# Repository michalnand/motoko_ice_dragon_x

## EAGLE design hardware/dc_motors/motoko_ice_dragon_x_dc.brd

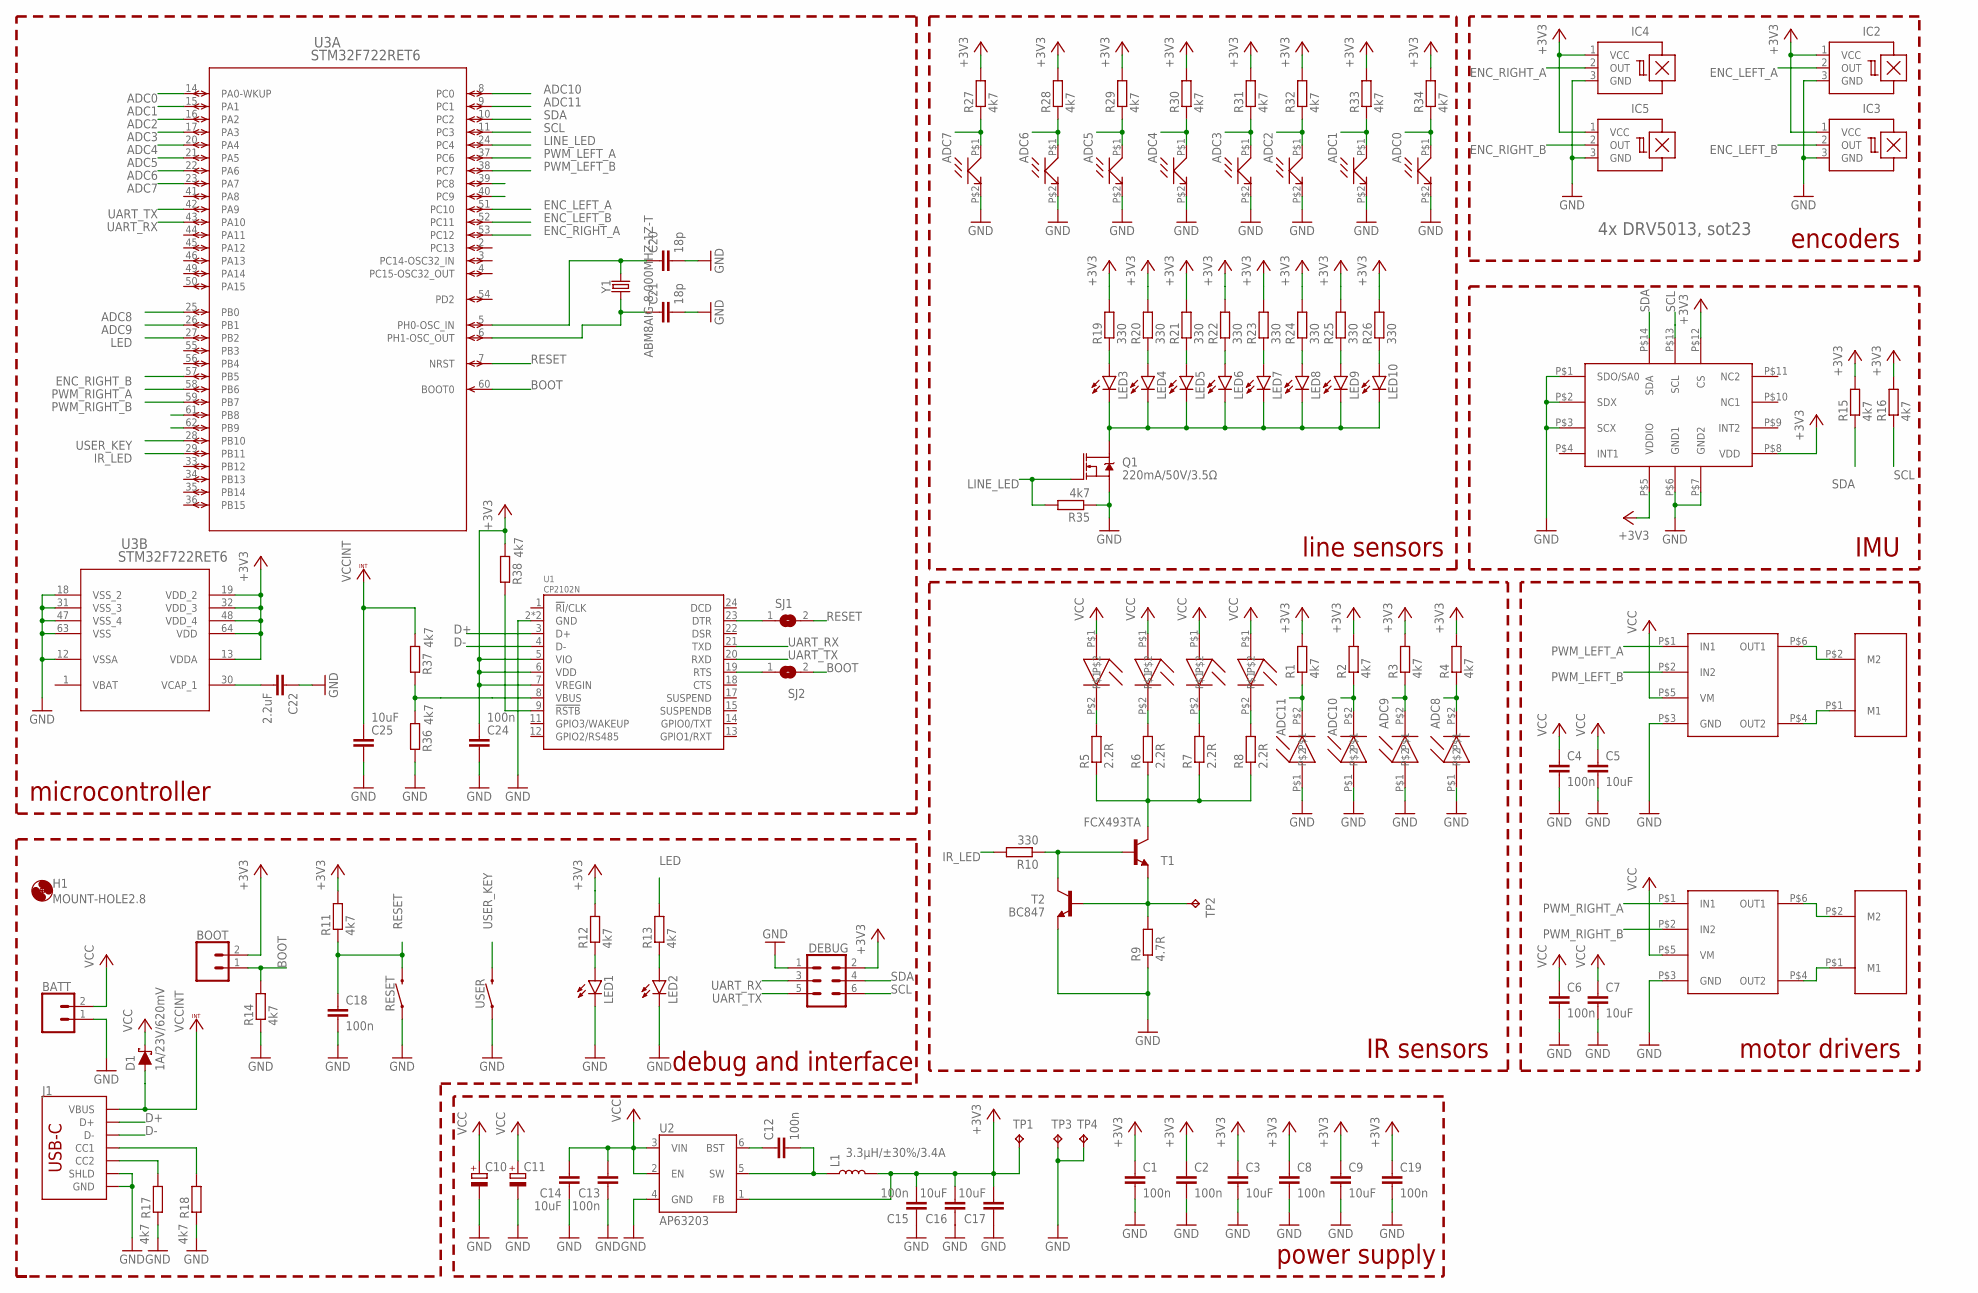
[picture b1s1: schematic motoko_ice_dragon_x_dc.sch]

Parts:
BATT: CONN_02LOCK_LONGPADS; 1X02_LOCK_LONGPADS
BOOT: CONN_02LOCK_LONGPADS; 1X02_LOCK_LONGPADS
C1, C2, C4, C6, C8, C12, C13, C15, C18, C19, C24: 100n; C0805
C3, C5, C7, C9, C14, C16, C17, C25: 10uF; C0805
C10, C11: CPOL-EU140CLH-0810; 140CLH-0810
C20, C21: 18p; C0805
C22: 2.2uF; C0805
D1: 1A/23V/620mV; SOD-323
DEBUG: FEMALE 2x3; 2X3
H1: MOUNT-HOLE2.8; 2,8
IC2, IC3, IC4, IC5: A1202LH; SOT23-W
J1: 640-USB4105-GF-A-120, man. GCT; USB-C-16P-2LAYER-PADS
L1: 3.3µH/±30%/3.4A; CR54
LED1, LED2, LED3, LED4, LED5, LED6, LED7, LED8, LED9, LED10: LEDCHIPLED_1206; CHIPLED_1206
Q1: 220mA/50V/3.5Ω; SOT23-3
R1, R2, R3, R4, R11, R12, R13, R14, R15, R16, R17, R18, R27, R28, R29, R30, R31, R32, R33, R34, R35, R36, R37, R38: 4k7; M0805
R5, R6, R7, R8: 2.2R; M0805
R9: 4.7R; M0805
R10, R19, R20, R21, R22, R23, R24, R25, R26: 330; M0805
RESET: MOMENTARY-SWITCH-SPST-SMD-6.2MM-TALL; TACTILE_SWITCH_SMD_6.2MM_TALL
SJ1, SJ2: SJ
T1: FCX493TA; SOT89-BCE
T2: BC847; SOT23
TP1, TP2, TP3, TP4: TPB1,27; B1,27
U1: CP2102N; QFN24
U2: AP63203; SOT23-6
U3: STM32F722RET6; LQFP64-10X10MM
U$1, U$3: DRV8212; SOT_0.6MM
U$2, U$15, U$16, U$17, U$18, U$19, U$20, U$21: SFH3710; SFH710
U$4, U$5: POLOLU_MICRO_METAL_GEAR_MOTOR
U$6: LSM6DSM; LGA14L
U$7, U$8, U$9, U$10, U$11, U$12, U$13, U$14: LED_5MM_AXIAL
USER: MOMENTARY-SWITCH-SPST-SMD-6.2MM-TALL; TACTILE_SWITCH_SMD_6.2MM_TALL
Y1: ABM8AIG-8.000MHZ-1Z-T; CRYSTAL-SMD-3.2X2.5MM

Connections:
+3V3: BOOT.2, C1.1, C2.1, C3.1, C8.1, C9.1, C15.2, C16.2, C17.2, C19.1, C24.1, DEBUG.2, IC2.1 (VCC), IC3.1 (VCC), IC4.1 (VCC), IC5.1 (VCC), L1.P$2 (2), R1.2, R2.2, R3.2, R4.2, R11.2, R12.2, R15.2, R16.2, R19.2, R20.2, R21.2, R22.2, R23.2, R24.2, R25.2, R26.2, R27.2, R28.2, R29.2, R30.2, R31.2, R32.2, R33.2, R34.2, R38.1, TP1.TP, U1.5 (VIO), U1.6 (VDD), U1.7 (VREGIN), U2.1 (FB), U3.13 (VDDA), U3.19 (VDD_2), U3.32 (VDD_3), U3.48 (VDD_4), U3.64 (VDD), U$6.P$5 (VDDIO), U$6.P$8 (VDD), U$6.P$12 (CS)
ADC0: R34.1, U3.14 (PA0-WKUP), U$21.P$1 (C)
ADC1: R33.1, U3.15 (PA1), U$20.P$1 (C)
ADC2: R32.1, U3.16 (PA2), U$19.P$1 (C)
ADC3: R31.1, U3.17 (PA3), U$18.P$1 (C)
ADC4: R30.1, U3.20 (PA4), U$17.P$1 (C)
ADC5: R29.1, U3.21 (PA5), U$16.P$1 (C)
ADC6: R28.1, U3.22 (PA6), U$15.P$1 (C)
ADC7: R27.1, U3.23 (PA7), U$2.P$1 (C)
ADC8: R4.1, U3.25 (PB0), U$7.P$2
ADC9: R3.1, U3.26 (PB1), U$11.P$2
ADC10: R2.1, U3.8 (PC0), U$14.P$2
ADC11: R1.1, U3.9 (PC1), U$9.P$2
BOOT: BOOT.1, R14.2, SJ2.2, U3.60 (BOOT0)
D+: J1.A6 (D+), J1.B6 (D+), U1.3 (D+)
D-: J1.A7 (D-), J1.B7 (D-), U1.4 (D-)
ENC_LEFT_A: IC2.2 (OUT), U3.51 (PC10)
ENC_LEFT_B: IC3.2 (OUT), U3.52 (PC11)
ENC_RIGHT_A: IC4.2 (OUT), U3.53 (PC12)
ENC_RIGHT_B: IC5.2 (OUT), U3.57 (PB5)
GND: BATT.1, C1.2, C2.2, C3.2, C4.2, C5.2, C6.2, C7.2, C8.2, C9.2, C10.-, C11.-, C13.1, C14.1, C15.1, C16.1, C17.1, C18.2, C19.2, C20.2, C21.2, C22.1, C24.2, C25.2, DEBUG.1, IC2.3 (GND), IC3.3 (GND), IC4.3 (GND), IC5.3 (GND), J1.GND, J1.GND2 (GND), J1.SHLD1 (SHLD), J1.SHLD2 (SHLD), J1.SHLD3 (SHLD), J1.SHLD4 (SHLD), LED1.C, LED2.C, Q1.2 (S), R9.1, R14.1, R17.1, R18.1, R35.1, R36.2, RESET.A2 (1), T2.2 (E), TP3.TP, TP4.TP, U1.2 (GND), U1.PAD (GND), U2.4 (GND), U3.12 (VSSA), U3.18 (VSS_2), U3.31 (VSS_3), U3.47 (VSS_4), U3.63 (VSS), U$1.P$3 (GND), U$2.P$2 (E), U$3.P$3 (GND), U$6.P$1 (SDO/SA0), U$6.P$2 (SDX), U$6.P$3 (SCX), U$6.P$6 (GND1), U$6.P$7 (GND2), U$7.P$1, U$9.P$1, U$11.P$1, U$14.P$1, U$15.P$2 (E), U$16.P$2 (E), U$17.P$2 (E), U$18.P$2 (E), U$19.P$2 (E), U$20.P$2 (E), U$21.P$2 (E), USER.A2 (1)
IR_LED: R10.2, U3.29 (PB11)
LED: R13.2, U3.27 (PB2)
LINE_LED: Q1.1 (G), R35.2, U3.24 (PC4)
unnamed: U$1.P$6 (OUT1), U$4.P$2 (M2)
unnamed: U$1.P$4 (OUT2), U$4.P$1 (M1)
unnamed: U$3.P$6 (OUT1), U$5.P$2 (M2)
unnamed: U$3.P$4 (OUT2), U$5.P$1 (M1)
unnamed: R5.2, U$10.P$2
unnamed: R6.2, U$13.P$2
unnamed: R7.2, U$12.P$2
unnamed: R8.2, U$8.P$2
unnamed: SJ2.1, U1.19 (RTS)
unnamed: R9.2, T1.E, T2.1 (B), TP2.TP
unnamed: J1.B5 (CC2), R17.2
unnamed: C12.1, U2.6 (BST)
unnamed: C12.2, L1.P$1 (1), U2.5 (SW)
unnamed: R10.1, T1.B, T2.3 (C)
unnamed: R5.1, R6.1, R7.1, R8.1, T1.C
unnamed: LED1.A, R12.1
unnamed: LED2.A, R13.1
unnamed: J1.A5 (CC1), R18.2
unnamed: C20.1, U3.5 (PH0-OSC_IN), Y1.3 (2)
unnamed: C21.1, U3.6 (PH1-OSC_OUT), Y1.1
unnamed: LED3.A, R19.1
unnamed: LED4.A, R20.1
unnamed: C22.2, U3.30 (VCAP_1)
unnamed: LED5.A, R21.1
unnamed: LED6.A, R22.1
unnamed: LED7.A, R23.1
unnamed: LED8.A, R24.1
unnamed: LED9.A, R25.1
unnamed: LED10.A, R26.1
unnamed: LED3.C, LED4.C, LED5.C, LED6.C, LED7.C, LED8.C, LED9.C, LED10.C, Q1.3 (D)
unnamed: SJ1.1, U1.23 (DTR)
unnamed: R38.2, U1.9 (!RSTB)
unnamed: R36.1, R37.2, U1.8 (VBUS)
PWM_LEFT_A: U3.37 (PC6), U$1.P$1 (IN1)
PWM_LEFT_B: U3.38 (PC7), U$1.P$2 (IN2)
PWM_RIGHT_A: U3.58 (PB6), U$3.P$1 (IN1)
PWM_RIGHT_B: U3.59 (PB7), U$3.P$2 (IN2)
RESET: C18.1, R11.1, RESET.B2 (2), SJ1.2, U3.7 (NRST)
SCL: DEBUG.6, R16.1, U3.11 (PC3), U$6.P$13 (SCL)
SDA: DEBUG.4, R15.1, U3.10 (PC2), U$6.P$14 (SDA)
UART_RX: DEBUG.3, U1.21 (TXD), U3.43 (PA10)
UART_TX: DEBUG.5, U1.20 (RXD), U3.42 (PA9)
USER_KEY: U3.28 (PB10), USER.B2 (2)
VBAT: U3.1 (VBAT)
VCC: BATT.2, C4.1, C5.1, C6.1, C7.1, C10.+, C11.+, C13.2, C14.2, D1.C, U2.2 (EN), U2.3 (VIN), U$1.P$5 (VM), U$3.P$5 (VM), U$8.P$1, U$10.P$1, U$12.P$1, U$13.P$1
VCCINT: C25.1, D1.A, J1.VBUS1 (VBUS), J1.VBUS2 (VBUS), R37.1

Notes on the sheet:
4x DRV5013, sot23
line sensors
encoders
IMU
motor drivers
IR sensors
power supply
debug and interface
microcontroller

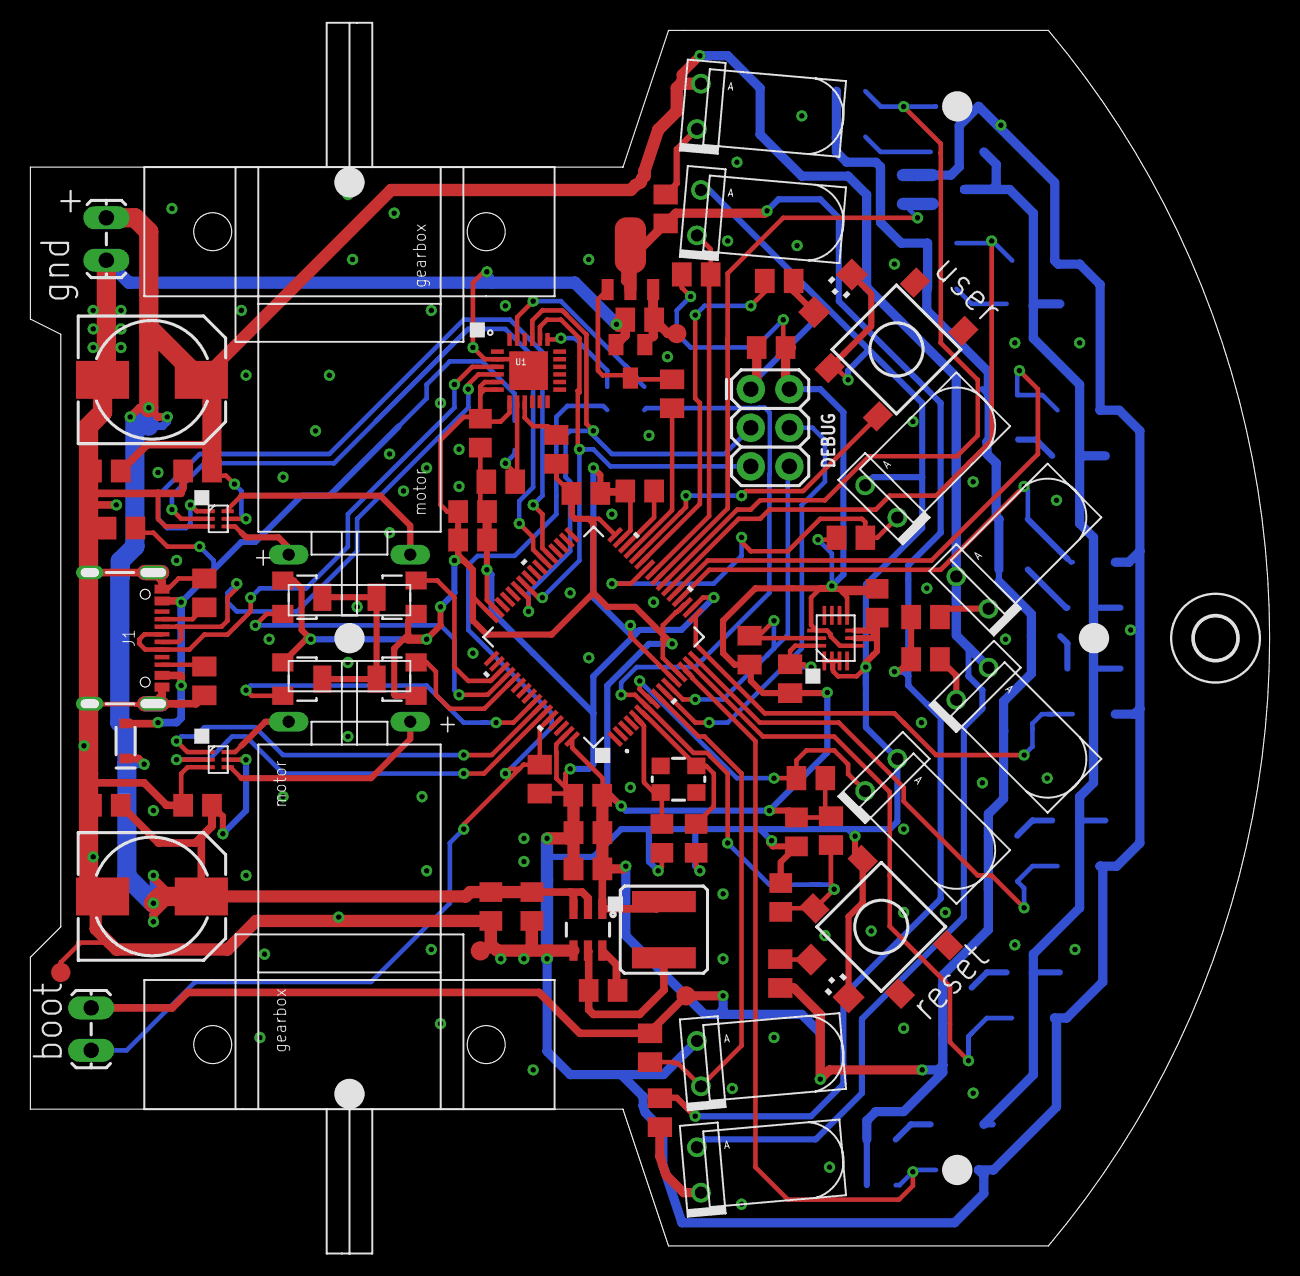
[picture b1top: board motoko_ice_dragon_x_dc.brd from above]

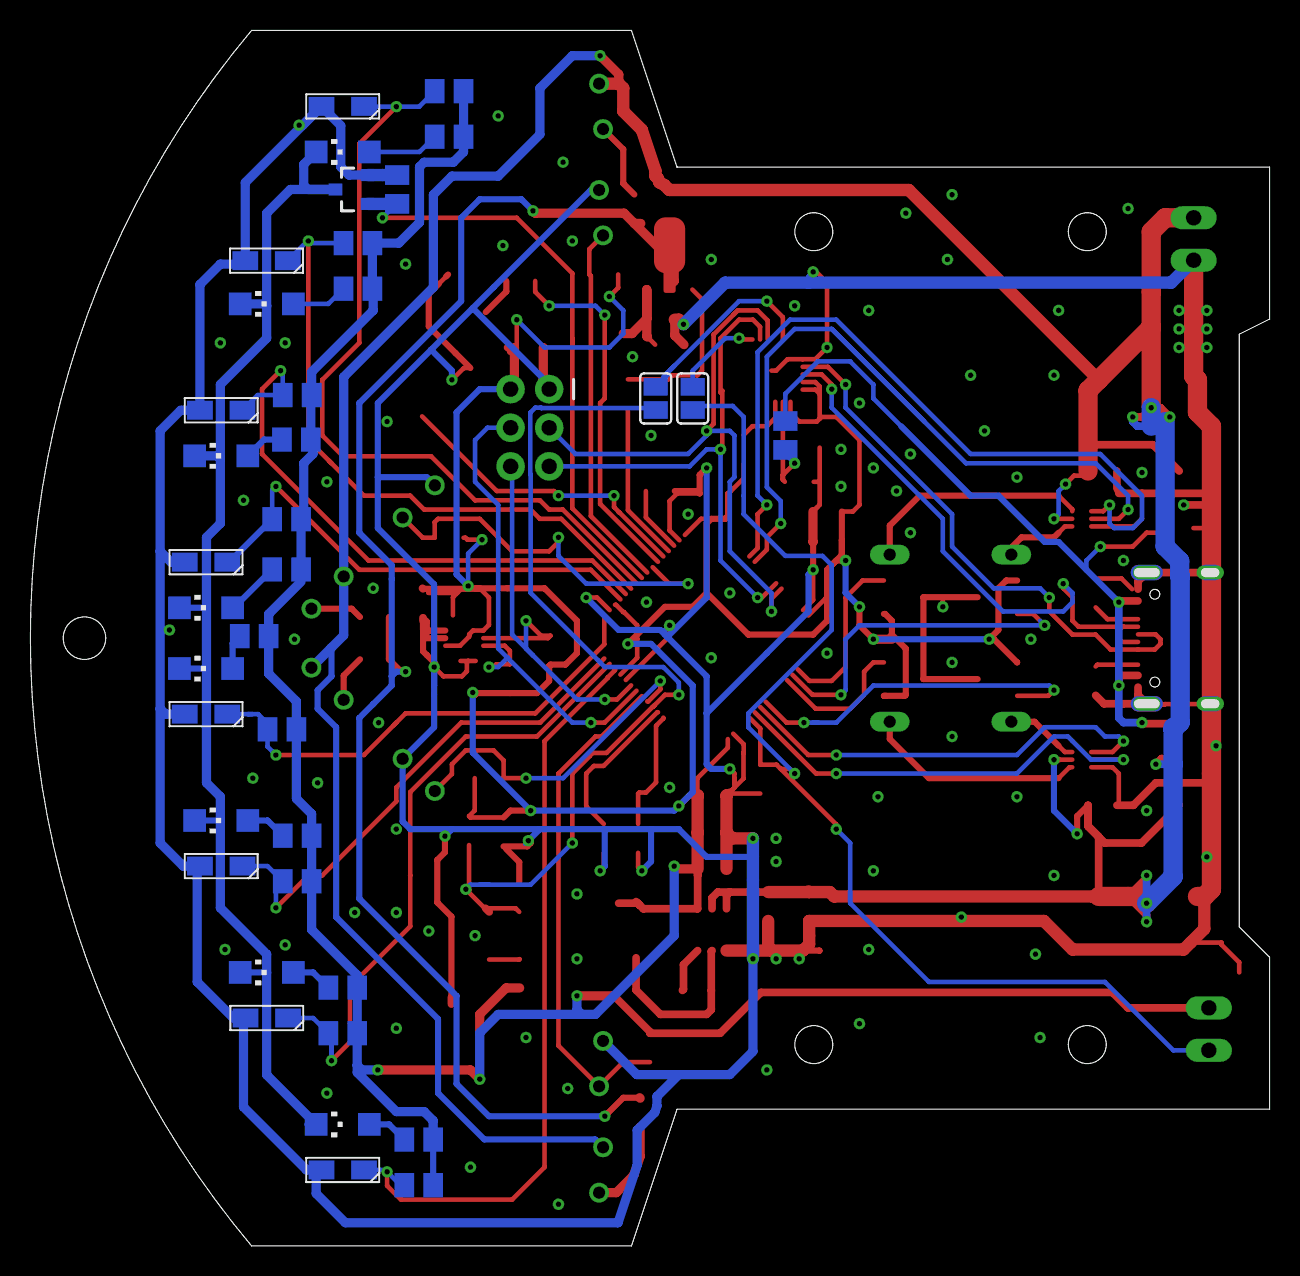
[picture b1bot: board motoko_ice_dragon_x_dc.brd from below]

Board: 2 copper layers, 81.0 x 79.4 mm, 119 parts (37 on the bottom side), 69 nets.

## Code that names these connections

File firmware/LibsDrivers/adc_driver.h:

#ifndef _ADC_DRIVER_H_
#define _ADC_DRIVER_H_ 

#define ADC_CHANNELS_COUNT      ((uint32_t)(8 + 4))

#define LINE_SENSOR_OFFSET      ((uint32_t)(0))
#define IR_SENSOR_OFFSET        ((uint32_t)(8))


//line sensors physical channels
#define ADC_LINE_0                 (LL_ADC_CHANNEL_0)    //PA0   - right sensor
#define ADC_LINE_1                 (LL_ADC_CHANNEL_1)    //PA1
#define ADC_LINE_2                 (LL_ADC_CHANNEL_2)    //PA2
#define ADC_LINE_3                 (LL_ADC_CHANNEL_3)    //PA3
#define ADC_LINE_4                 (LL_ADC_CHANNEL_4)    //PA4
#define ADC_LINE_5                 (LL_ADC_CHANNEL_5)    //PA5
#define ADC_LINE_6                 (LL_ADC_CHANNEL_6)    //PA6
#define ADC_LINE_7                 (LL_ADC_CHANNEL_7)    //PA7   - left sensor

//IR sensors physical channels
#define ADC_IR_FRONT_LEFT           (LL_ADC_CHANNEL_8)    //PB0
#define ADC_IR_LEFT                 (LL_ADC_CHANNEL_9)    //PB1
#define ADC_IR_RIGHT                (LL_ADC_CHANNEL_10)   //PC0
#define ADC_IR_FRONT_RIGHT          (LL_ADC_CHANNEL_11)   //PC1

  
class ADC_driver
{
    public:
        ADC_driver();

        void init();
        uint16_t* get();

        void callback();

    public:    
        uint32_t adc_current_idx;
        uint32_t adc_channels[ADC_CHANNELS_COUNT];
        uint16_t adc_result[ADC_CHANNELS_COUNT];

        uint32_t measurement_id;
};

#endif

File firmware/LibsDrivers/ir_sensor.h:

#ifndef _IR_SENSOR_H_
#define _IR_SENSOR_H_

#include <drivers.h>
#include <stdint.h>
#include <array.h>


#define IR_SENSORS_COUNT        ((unsigned int)4)


/*
    IR left         :   PB1     ADC1, ADC2, IN9
    IR front left   :   PC5     ADC1, ADC2, IN15
    IR front right  :   PC4     ADC1, ADC2, IN14
    IR right        :   PB0     ADC1, ADC2, IN8
*/

class IRSensor
{
    public:
        void init();

        void callback();

        float obstacle_distance();
        int obstacle_detected();
            
    private:
        float calibration(float *callibration, float x);

    public:
        uint32_t measurement_id;

    private: 
        uint32_t state;
        Gpio<'B', 11, GPIO_MODE_OUT> ir_led; 

        Array<int, IR_SENSORS_COUNT> ir_off;
        Array<int, IR_SENSORS_COUNT> ir_on;

        float filter_coeff;
            
    public:
        Array<float, IR_SENSORS_COUNT> distance;

};

#endif

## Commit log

2024-06-15 initial + hw
2024-06-15 documentation
2024-06-16 firmware
2024-06-16 bldc version
2024-06-19 firmware tests
2024-06-19 tests
2024-06-20 tests + images
2024-06-21 ir sensors
2024-06-23 encoder fix
2024-07-18 simulation
2024-07-30 demos + tests
2024-08-07 motor control, motor identification
2024-08-08 identification demo
2024-08-15 better encoder
2024-09-15 pid example
2024-10-28 kalman filter for encoder
2024-10-29 motor test
2024-11-22 bldc test
2024-11-26 mpc simulation
2025-03-02 position control
2025-03-10 position controller, model identifiction
2025-03-13 new motor control
2025-03-14 path planner
2025-03-15 acc control
2025-03-18 line following
2025-03-23 mpc line following
2025-03-27 fast line following
2025-03-30 line following + broken line
2025-04-01 brick avoid
2025-04-04 line follower
2025-04-21 working code
2025-04-26 istrobot 2025 final round
2025-11-20 cleaned up firmware, work in progress
2025-11-21 add tests, motor driver, adc
2025-11-22 drivers
2025-11-23 bldc sinusoidal control
2025-11-24 velocity control
2025-11-30 controller fix

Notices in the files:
parts and their libraries:
my_library: COPYRIGHT: Copyright (C) 2024 Ultra Librarian. All rights reserved.
SparkFun-Connectors: Licensing: Creative Commons ShareAlike 4.0 International - https://creativecommons.org/licenses/by-sa/4.0
